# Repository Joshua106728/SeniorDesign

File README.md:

Aimed at helping composers and music learners transcribe music, Ear2Ink is a portable embedded system designed to convert acoustic guitar performances into MIDI files in real time. The device captures audio through a digital microphone, processes the signals on a microcontroller, and stores the resulting data on an SD card for sheet music generation. A keypad interface allows the user to start and stop recordings, and an LCD screen provides system feedback. By combining real-time audio processing with intuitive user interfacing, Ear2Ink offers musicians the freedom to transcribe and compose on the fly.

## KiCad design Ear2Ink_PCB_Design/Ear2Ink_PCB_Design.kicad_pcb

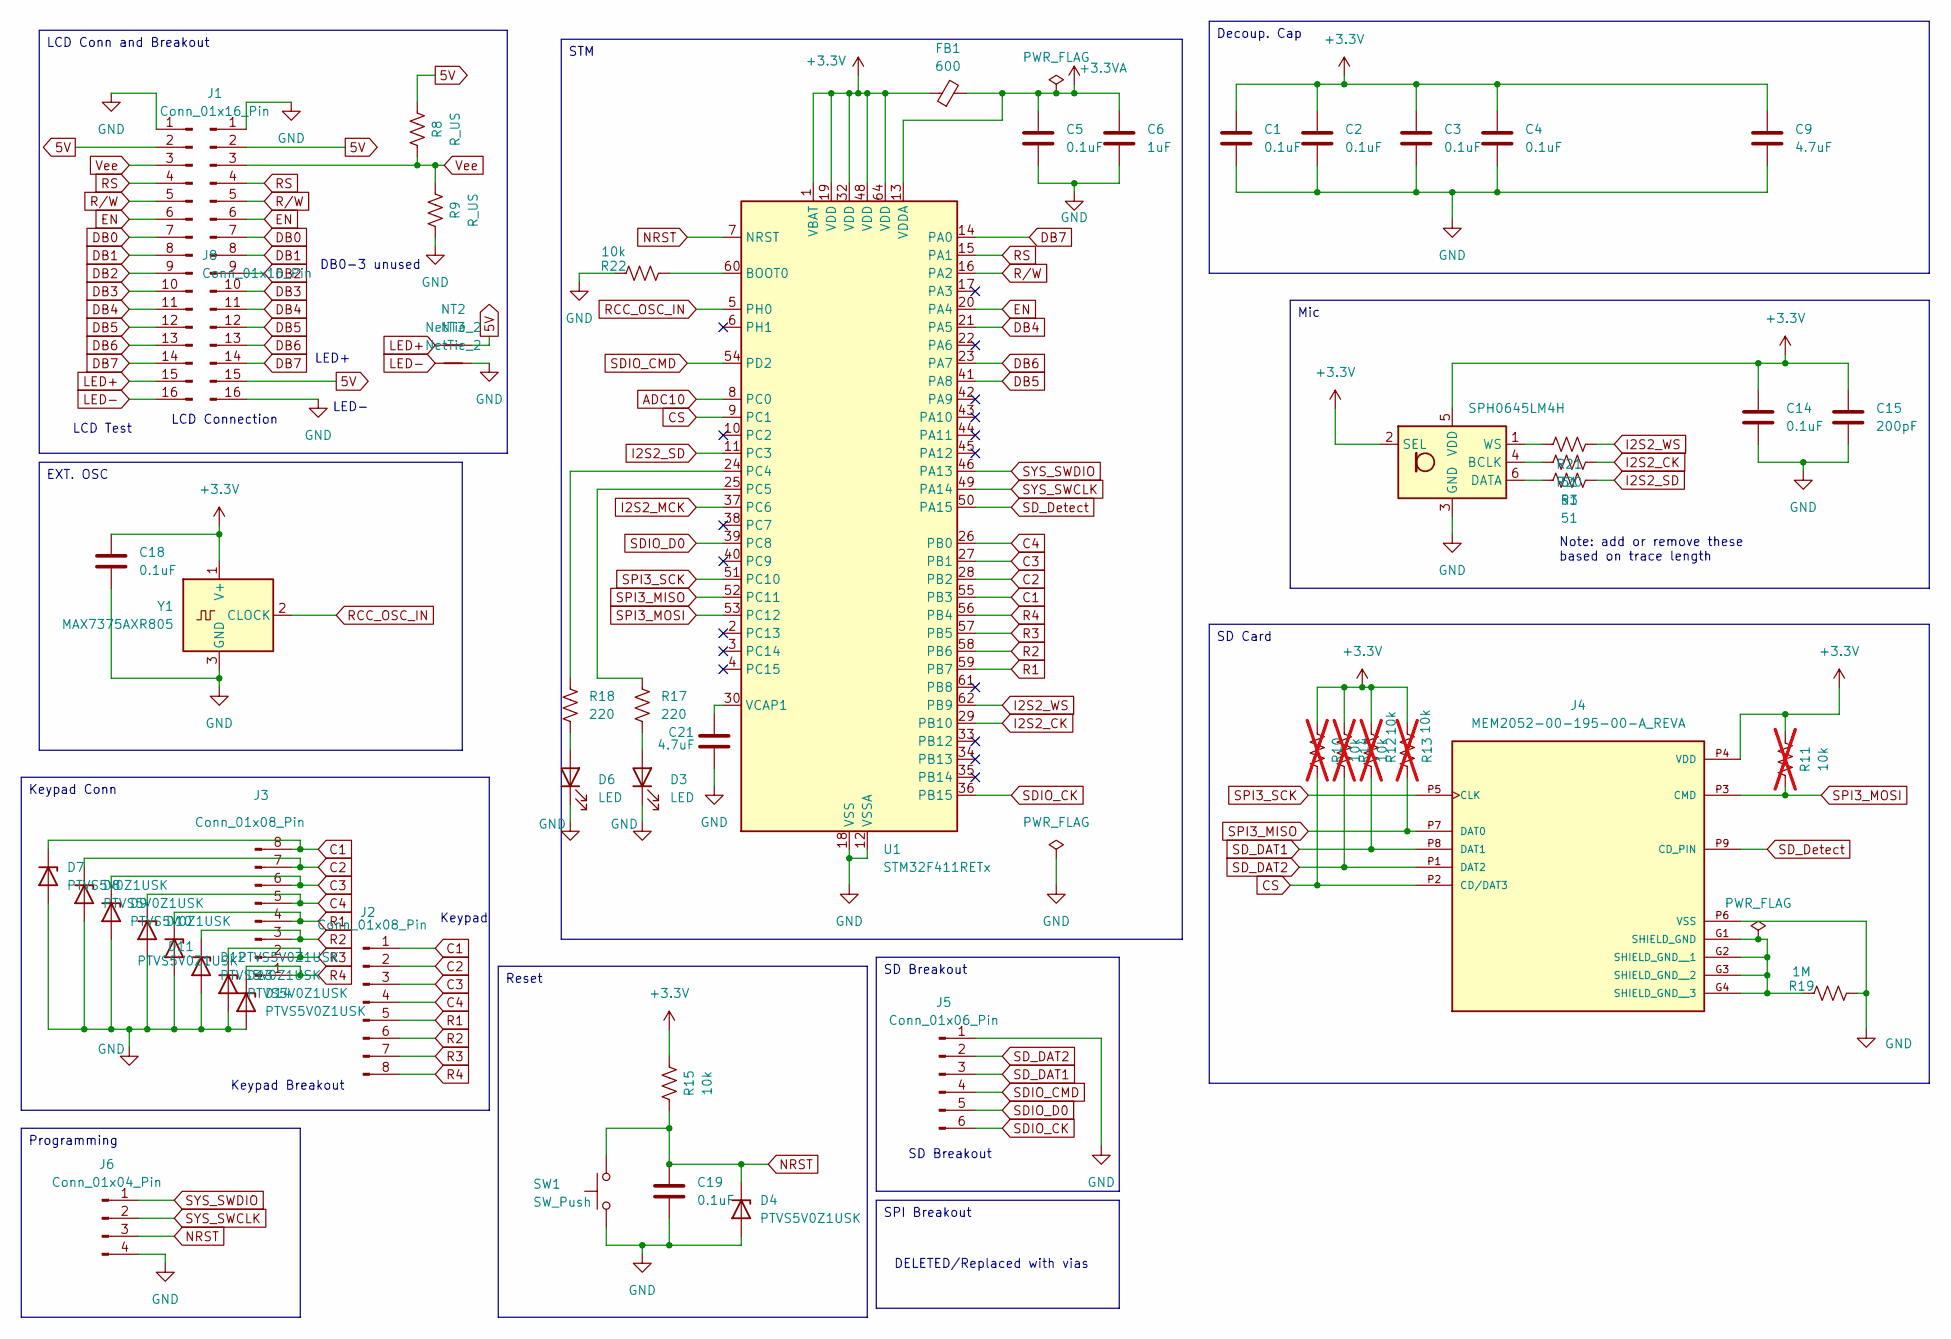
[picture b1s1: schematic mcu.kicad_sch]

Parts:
C1, C2, C3, C4, C5, C14, C18, C19: 0.1uF; C_0603_1608Metric_Pad1.08x0.95mm_HandSolder
C6: 1uF; C_0603_1608Metric_Pad1.08x0.95mm_HandSolder
C9, C21: 4.7uF; C_0603_1608Metric_Pad1.08x0.95mm_HandSolder
C15: 200pF; C_0805_2012Metric_Pad1.18x1.45mm_HandSolder
D3, D6: LED; LED_0805_2012Metric_Pad1.15x1.40mm_HandSolder
D4, D7, D8, D9, D10, D11, D12, D13, D14: PTVS5V0Z1USK; Nexperia_DSN1608-2_1.6x0.8mm
FB1: 600; R_0603_1608Metric_Pad0.98x0.95mm_HandSolder
J1, J8: Conn_01x16_Pin; PinHeader_1x16_P2.54mm_Vertical
J2, J3: Conn_01x08_Pin; PinHeader_1x08_P2.54mm_Vertical
J4: MEM2052-00-195-00-A_REVA; GCT_MEM2052-00-195-00-A_REVA; PARTREV A
J5: Conn_01x06_Pin; PinHeader_1x06_P2.54mm_Vertical
J6: Conn_01x04_Pin; PinHeader_1x04_P2.54mm_Vertical
MK1: SPH0645LM4H; Knowles_SPH0645LM4H-6_3.5x2.65mm
NT2, NT3: NetTie_2; NetTie-2_SMD_Pad0.5mm
R3, R20, R21: 51; R_0603_1608Metric_Pad0.98x0.95mm_HandSolder
R8, R9: R_US; R_0603_1608Metric_Pad0.98x0.95mm_HandSolder
R10, R11, R12, R13, R14: 10k; R_0603_1608Metric_Pad0.98x0.95mm_HandSolder; not fitted
R15, R22: 10k; R_0603_1608Metric_Pad0.98x0.95mm_HandSolder
R17, R18: 220; R_0603_1608Metric_Pad0.98x0.95mm_HandSolder
R19: 1M; R_0603_1608Metric_Pad0.98x0.95mm_HandSolder
SW1: SW_Push; SW_FSM2JMTR_TEC
U1: STM32F411RETx; LQFP64-10x10mm
Y1: MAX7375AXR805; SOT-323_SC-70

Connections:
5V: J1.2, J1.15, J8.2, NT2.2, R8.1; also elsewhere on the board
+3.3V: C1.1, C2.1, C3.1, C4.1, C9.1, C14.1, C15.1, C18.1, FB1.1, J4.P4 (VDD), MK1.2 (SEL), MK1.5 (VDD), R10.1, R11.1, R12.1, R13.1, R14.1, R15.1, U1.1 (VBAT), U1.19 (VDD), U1.32 (VDD), U1.48 (VDD), U1.64 (VDD), Y1.1 (V+); also elsewhere on the board
+3.3VA: C5.1, C6.1, FB1.2, U1.13 (VDDA)
ADC10: U1.8 (PC0); also elsewhere on the board
C1: D7.1 (K), J2.1, J3.8, U1.55 (PB3)
C2: D8.1 (K), J2.2, J3.7, U1.28 (PB2)
C3: D9.1 (K), J2.3, J3.6, U1.27 (PB1)
C4: D10.1 (K), J2.4, J3.5, U1.26 (PB0)
CS: J4.P2 (CD/DAT3), R10.2, U1.9 (PC1)
DB0: J1.7, J8.7
DB1: J1.8, J8.8
DB2: J1.9, J8.9
DB3: J1.10, J8.10
DB4: J1.11, J8.11, U1.21 (PA5)
DB5: J1.12, J8.12, U1.41 (PA8)
DB6: J1.13, J8.13, U1.23 (PA7)
DB7: J1.14, J8.14, U1.14 (PA0)
EN: J1.6, J8.6, U1.20 (PA4)
GND: C1.2, C2.2, C3.2, C4.2, C5.2, C6.2, C9.2, C14.2, C15.2, C18.2, C19.2, C21.2, D3.1 (K), D4.2 (A), D6.1 (K), D7.2 (A), D8.2 (A), D9.2 (A), D10.2 (A), D11.2 (A), D12.2 (A), D13.2 (A), D14.2 (A), J1.1, J1.16, J4.P6 (VSS), J5.1, J6.4, J8.1, MK1.3 (GND), NT3.2, R9.2, R19.2, R22.1, SW1.1, U1.12 (VSSA), U1.18 (VSS), U1.31 (VSS), U1.47 (VSS), U1.63 (VSS), Y1.3 (GND); also elsewhere on the board
I2S2_CK: R20.1, U1.29 (PB10)
I2S2_MCK: U1.37 (PC6)
I2S2_SD: R3.1, U1.11 (PC3)
I2S2_WS: R21.1, U1.62 (PB9)
LED+: J8.15, NT2.1
LED-: J8.16, NT3.1
NRST: C19.1, D4.1 (K), J6.3, R15.2, SW1.2, U1.7 (NRST)
unnamed: D3.2 (A), R17.2
unnamed: D6.2 (A), R18.2
unnamed: J4.G1 (SHIELD_GND), J4.G2 (SHIELD_GND__1), J4.G3 (SHIELD_GND__2), J4.G4 (SHIELD_GND__3), R19.1
unnamed: MK1.4 (BCLK), R20.2
unnamed: MK1.6 (DATA), R3.2
unnamed: MK1.1 (WS), R21.2
unnamed: R22.2, U1.60 (BOOT0)
unnamed: R18.1, U1.24 (PC4)
unnamed: R17.1, U1.25 (PC5)
unnamed: C21.1, U1.30 (VCAP1)
R1: D11.1 (K), J2.5, J3.4, U1.59 (PB7)
R2: D12.1 (K), J2.6, J3.3, U1.58 (PB6)
R3: D13.1 (K), J2.7, J3.2, U1.57 (PB5)
R4: D14.1 (K), J2.8, J3.1, U1.56 (PB4)
RCC_OSC_IN: U1.5 (PH0), Y1.2 (CLOCK)
RS: J1.4, J8.4, U1.15 (PA1)
R/W: J1.5, J8.5, U1.16 (PA2)
SDIO_CK: J5.6, U1.36 (PB15)
SDIO_CMD: J5.4, U1.54 (PD2)
SDIO_D0: J5.5, U1.39 (PC8)
SD_DAT1: J4.P8 (DAT1), J5.3, R12.2
SD_DAT2: J4.P1 (DAT2), J5.2, R14.2
SD_Detect: J4.P9 (CD_PIN), U1.50 (PA15)
SPI3_MISO: J4.P7 (DAT0), R13.2, U1.52 (PC11)
SPI3_MOSI: J4.P3 (CMD), R11.2, U1.53 (PC12)
SPI3_SCK: J4.P5 (CLK), U1.51 (PC10)
SYS_SWCLK: J6.2, U1.49 (PA14)
SYS_SWDIO: J6.1, U1.46 (PA13)
Vee: J1.3, J8.3, R8.2, R9.1

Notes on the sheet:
LED+
LCD Connection
Note: add or remove these based on trace length
LCD Test
LED-
SD Breakout
DELETED/Replaced with vias
DB0-3 unused
Keypad Breakout
Keypad
Mic
Keypad Conn
STM
Reset
Programming
SD Card
LCD Conn and Breakout
SPI Breakout
EXT. OSC
Decoup. Cap

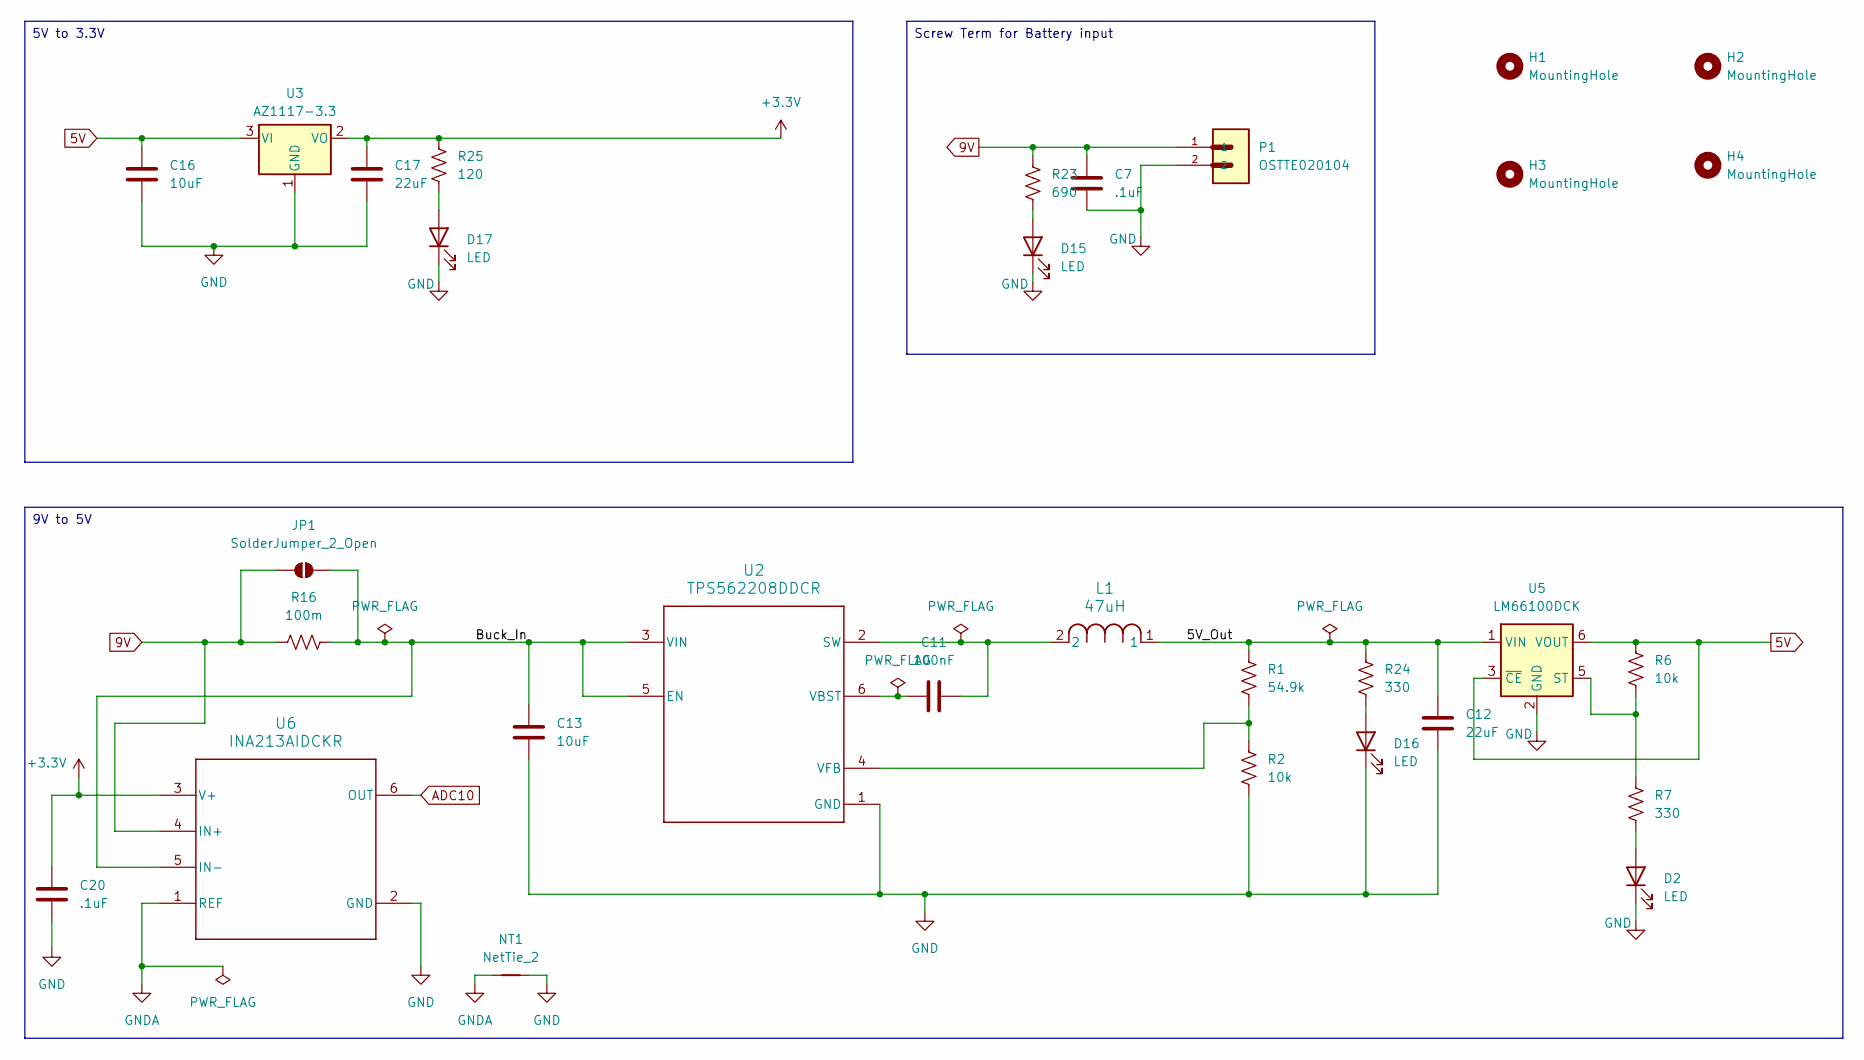
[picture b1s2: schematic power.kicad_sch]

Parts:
C7, C20: .1uF; C_0603_1608Metric_Pad1.08x0.95mm_HandSolder
C11: 100nF; C_0603_1608Metric_Pad1.08x0.95mm_HandSolder
C12, C17: 22uF; C_0603_1608Metric_Pad1.08x0.95mm_HandSolder
C13, C16: 10uF; C_0603_1608Metric_Pad1.08x0.95mm_HandSolder
D2, D15, D16, D17: LED; LED_0805_2012Metric_Pad1.15x1.40mm_HandSolder
H1, H2, H3, H4: MountingHole; MountingHole_2.5mm
JP1: SolderJumper_2_Open; SolderJumper-2_P1.3mm_Open_Pad1.0x1.5mm
L1: 47uH; L_Vishay_IFSC-1515AH_4x4x1.8mm
NT1: NetTie_2; NetTie-2_SMD_Pad0.5mm
P1: OSTTE020104; OST_OSTTE020104
R1: 54.9k; R_0603_1608Metric_Pad0.98x0.95mm_HandSolder
R2, R6: 10k; R_0603_1608Metric_Pad0.98x0.95mm_HandSolder
R7, R24: 330; R_0603_1608Metric_Pad0.98x0.95mm_HandSolder
R16: 100m; R_0603_1608Metric_Pad0.98x0.95mm_HandSolder
R23: 690; R_0603_1608Metric_Pad0.98x0.95mm_HandSolder
R25: 120; R_0603_1608Metric_Pad0.98x0.95mm_HandSolder
U2: TPS562208DDCR; DDC0006A_N
U3: AZ1117-3.3; SOT-223_DIO
U5: LM66100DCK; SOT-363_SC-70-6
U6: INA213AIDCKR; DCK0006A_N

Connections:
5V: C16.1, R6.1, U3.3 (VI), U5.3 (~CE), U5.6 (VOUT); also elsewhere on the board
9V: C7.2, JP1.1 (A), P1.1, R16.2, R23.1, U6.4 (IN+)
+3.3V: C17.1, C20.2, R25.1, U3.2 (VO), U6.3 (V+); also elsewhere on the board
/Power Conversions + Battery Monitor/5V_Out: C12.1, L1.1, R1.1, R24.1, U5.1 (VIN)
/Power Conversions + Battery Monitor/Buck_In: C13.2, JP1.2 (B), R16.1, U2.3 (VIN), U2.5 (EN), U6.5 (IN-)
ADC10: U6.6 (OUT); also elsewhere on the board
GND: C7.1, C12.2, C13.1, C16.2, C17.2, C20.1, D2.1 (K), D15.1 (K), D16.1 (K), D17.1 (K), NT1.2, P1.2, R2.2, U2.1 (GND), U3.1 (GND), U5.2 (GND), U6.2 (GND); also elsewhere on the board
GNDA: NT1.1, U6.1 (REF)
unnamed: D2.2 (A), R7.2
unnamed: D15.2 (A), R23.2
unnamed: D16.2 (A), R24.2
unnamed: D17.2 (A), R25.2
unnamed: C11.2, L1.2, U2.2 (SW)
unnamed: C11.1, U2.6 (VBST)
unnamed: R1.2, R2.1, U2.4 (VFB)
unnamed: R6.2, R7.1, U5.5 (ST)

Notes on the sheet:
Screw Term for Battery input
9V to 5V
5V to 3.3V

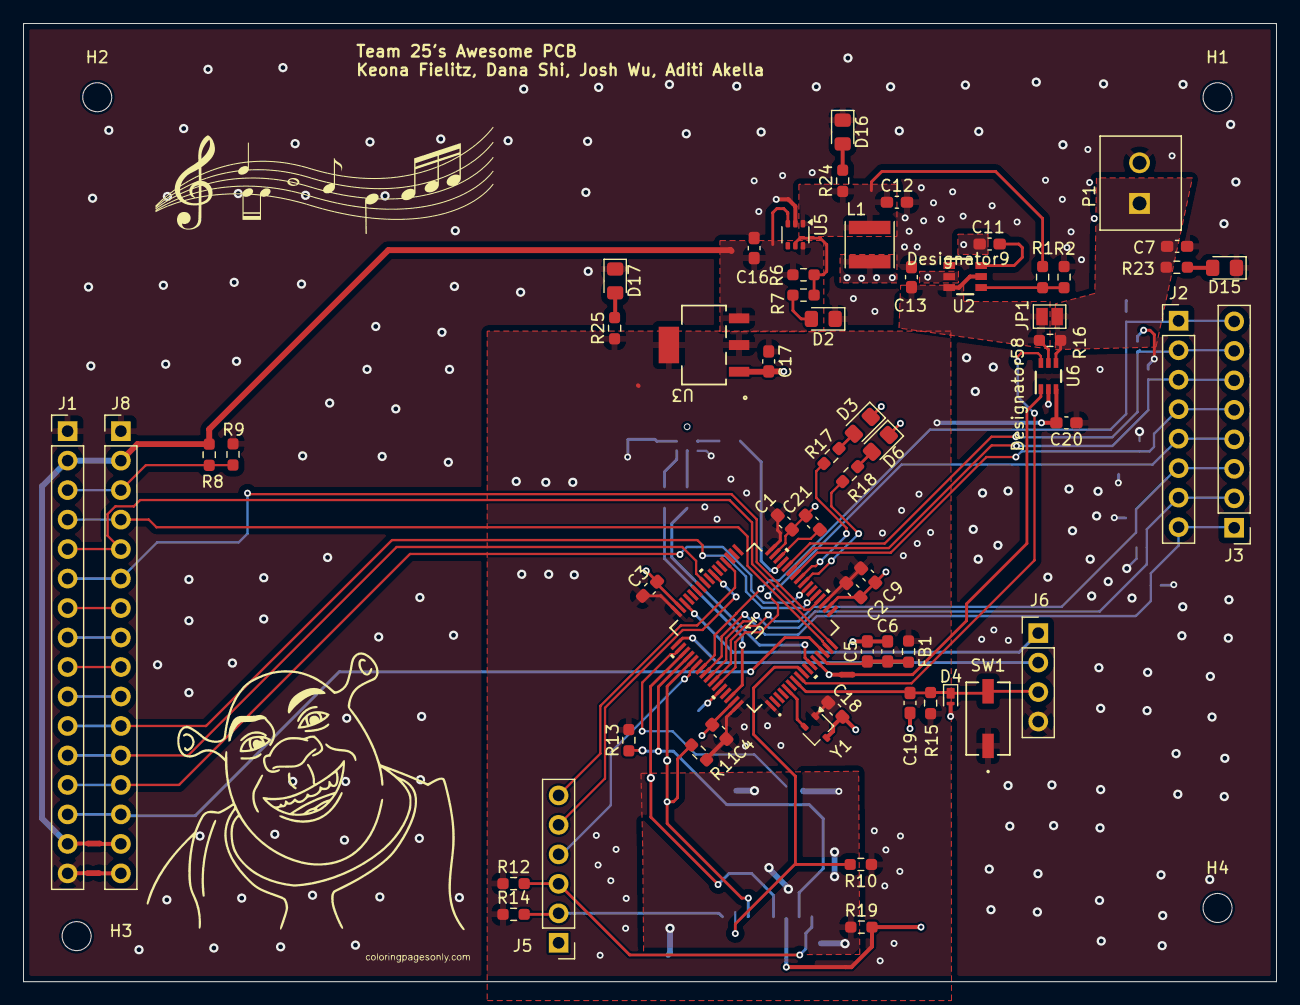
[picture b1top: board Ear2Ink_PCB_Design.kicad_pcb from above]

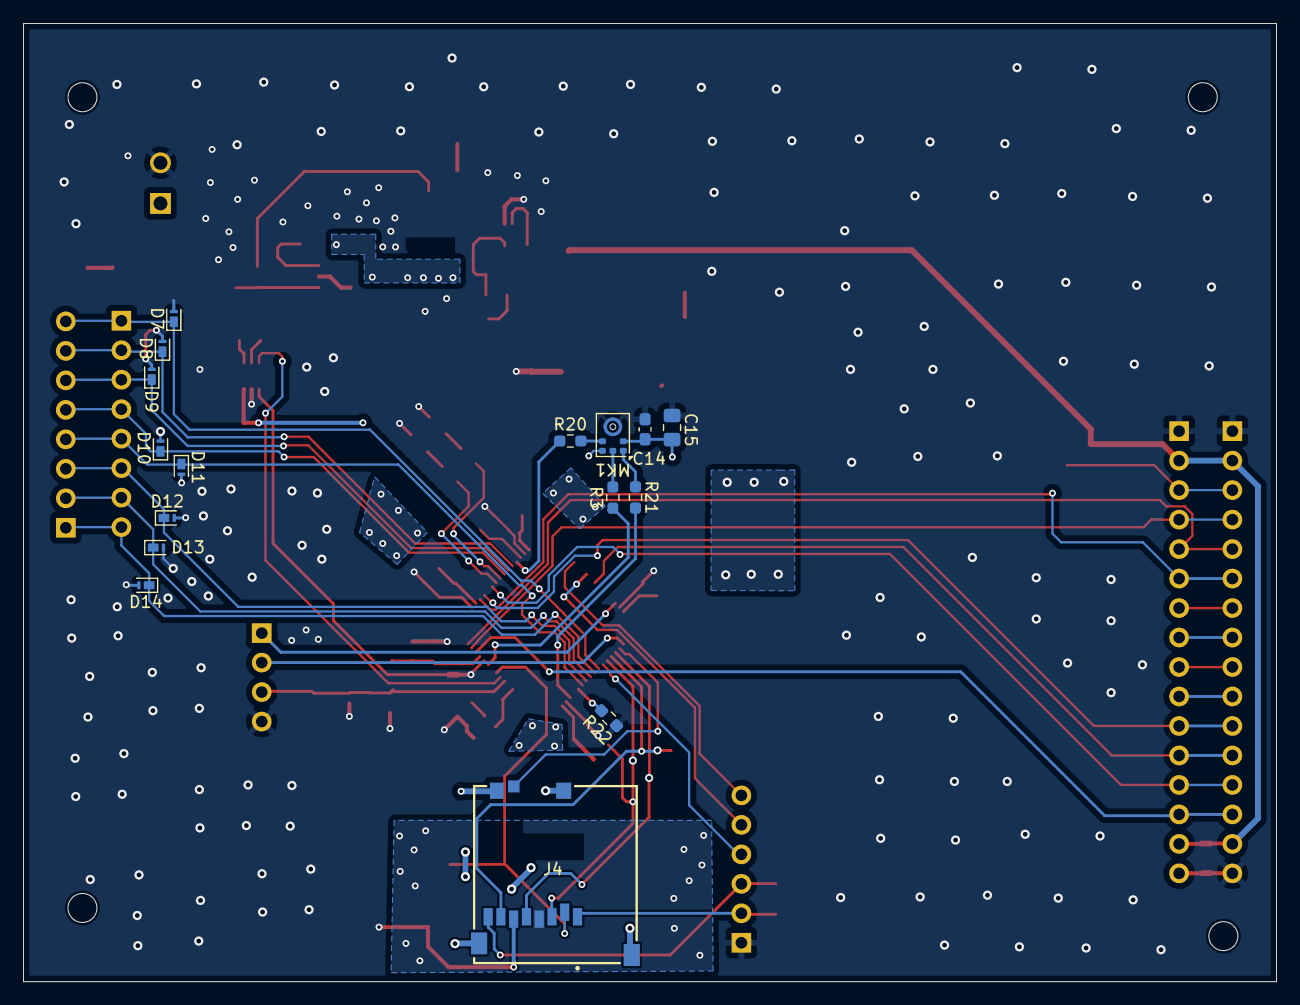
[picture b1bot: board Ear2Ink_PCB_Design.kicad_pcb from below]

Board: 2 copper layers, 108.0 x 82.5 mm, 83 parts (16 on the bottom side), 66 nets.

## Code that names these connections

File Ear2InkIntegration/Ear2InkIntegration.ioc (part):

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Mcu.Name=STM32F411R(C-E)Tx
Mcu.Package=LQFP64
Mcu.UserName=STM32F411RETx
PA0-WKUP.GPIOParameters=GPIO_Label
PA0-WKUP.GPIO_Label=DB7
PA0-WKUP.Signal=GPIO_Output
PA1.GPIOParameters=GPIO_Label
PA1.GPIO_Label=RS
PA1.Signal=GPIO_Output
PA13.Mode=Serial_Wire
PA13.Signal=SYS_JTMS-SWDIO
PA14.Mode=Serial_Wire
PA14.Signal=SYS_JTCK-SWCLK
PA15.GPIOParameters=GPIO_PuPd,GPIO_Label
PA15.GPIO_Label=SD_DETECT
PA15.GPIO_PuPd=GPIO_PULLUP
PA15.Signal=GPIO_Input
PA2.GPIOParameters=GPIO_Label
PA2.GPIO_Label=R/W
PA2.Signal=GPIO_Output
PA4.GPIOParameters=GPIO_Label
PA4.GPIO_Label=EN
PA4.Signal=GPIO_Output
PA5.GPIOParameters=GPIO_Label
PA5.GPIO_Label=DB4
PA5.Signal=GPIO_Output
PA7.GPIOParameters=GPIO_Label
PA7.GPIO_Label=DB6
PA7.Signal=GPIO_Output
PA8.GPIOParameters=GPIO_Label
PA8.GPIO_Label=DB5
PA8.Signal=GPIO_Output
PB0.GPIOParameters=GPIO_PuPd,GPIO_Label
PB0.GPIO_Label=C4
PB0.GPIO_PuPd=GPIO_PULLUP
PB0.Signal=GPIO_Input
PB1.GPIOParameters=GPIO_PuPd,GPIO_Label,GPIO_ModeDefaultEXTI
PB1.GPIO_Label=C3
PB1.GPIO_ModeDefaultEXTI=GPIO_MODE_IT_FALLING
PB1.GPIO_PuPd=GPIO_PULLUP
PB1.Signal=GPXTI1
PB10.Mode=Half_Duplex_Master
PB10.Signal=I2S2_CK
PB2.GPIOParameters=GPIO_PuPd,GPIO_Label
PB2.GPIO_Label=C2
PB2.GPIO_PuPd=GPIO_PULLUP
PB2.Signal=GPIO_Input
PB3.GPIOParameters=GPIO_PuPd,GPIO_Label,GPIO_ModeDefaultEXTI
PB3.GPIO_Label=C1
PB3.GPIO_ModeDefaultEXTI=GPIO_MODE_IT_FALLING
PB3.GPIO_PuPd=GPIO_PULLUP
PB3.Signal=GPXTI3
PB4.GPIOParameters=PinState,GPIO_Label
PB4.GPIO_Label=R4
PB4.PinState=GPIO_PIN_SET
PB4.Signal=GPIO_Output
PB5.GPIOParameters=PinState,GPIO_Label
PB5.GPIO_Label=R3
PB5.PinState=GPIO_PIN_SET
PB5.Signal=GPIO_Output
PB6.GPIOParameters=PinState,GPIO_Label
PB6.GPIO_Label=R2
PB6.PinState=GPIO_PIN_SET
PB6.Signal=GPIO_Output
PB7.GPIOParameters=PinState,GPIO_Label
PB7.GPIO_Label=R1
PB7.PinState=GPIO_PIN_SET
PB7.Signal=GPIO_Output
PB9.Mode=Half_Duplex_Master
PB9.Signal=I2S2_WS
PC1.GPIOParameters=PinState,GPIO_Label
PC1.GPIO_Label=CS
PC1.PinState=GPIO_PIN_SET
PC1.Signal=GPIO_Output
PC10.Mode=Full_Duplex_Master
PC10.Signal=SPI3_SCK
PC11.Mode=Full_Duplex_Master
PC11.Signal=SPI3_MISO
PC12.Mode=Full_Duplex_Master
PC12.Signal=SPI3_MOSI
PC3.Mode=Half_Duplex_Master
PC3.Signal=I2S2_SD
PC4.GPIOParameters=GPIO_Label
PC4.GPIO_Label=LED1
PC4.Signal=GPIO_Output
PC5.GPIOParameters=GPIO_Label
PC5.GPIO_Label=MET
PC5.Signal=GPIO_Output
RCC.HSE_VALUE=25000000
RCC.SYSCLKFreq_VALUE=96000000
RCC.SYSCLKSource=RCC_SYSCLKSOURCE_PLLCLK
board=custom

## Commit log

2025-10-01 initial push
    code contains a sine wave generator and currently just the YIN algorithm to detect fundamental frequency
2025-10-04 initial code
2025-10-07 time encoding in MIDI not correct HALP
2025-10-09 audo to midi not work still
2025-10-13 twinkle twinkle little stars working
2025-10-17 moving files
2026-01-22 Removed Python, added KiCad
2026-01-22 added buck
2026-01-23 added some stuff
2026-01-24 added osc
2026-01-26 added voltage prot
2026-01-31 wired LCD and keypad
2026-02-04 everything except voltage monitor on schematic
    no footprints assigned yet
2026-02-05 started assigning footprints
2026-02-05 added esd prot and programming header
2026-02-06 footprints
    missing L tho
2026-02-07 all footprints done
2026-02-07 added current monitor
2026-02-09 working on erc errors
2026-02-09 fixed erc stuff
2026-02-10 SDIO to SPI
2026-02-10 added zip file for archived proj
2026-02-11 fixed footprint issue with SD
2026-02-11 footprints loaded into pcb
2026-02-12 components on board (no traces yet)
2026-02-12 some routing
2026-02-14 some pcb
2026-02-15 more progress
2026-02-15 ran DRC and fixed some errors
2026-02-16 fixed everything
2026-02-16 added archived file
2026-02-17 changed some resistor values NEED To UPDATE LAYOUT
2026-02-17 resistors changed UPDATE LAYOUT
2026-02-27 New Parts Added
2026-02-27 Did a lot of stuff
2026-03-01 put everything on not done tho
    almost done
2026-03-02 working through DRC, routing done
2026-03-03 finshed routing and minimal drc
2026-03-03 made project archive for review
2026-03-06 done
2026-03-06 updated 5V resistor values
2026-03-06 archive
2026-03-07 untented vias added
2026-03-13 flipped SD to the other side
2026-03-13 added pic
2026-03-13 fab outputs
2026-03-25 working on python --> c wrapper
2026-03-31 all python should be working
2026-04-22 keylad lcd mic working - sd dsp need some work
2026-04-22 added midi file writing after stop is pressed
2026-04-30 final changes
2026-04-30 Add project overview to README.md
    Added project description for Ear2Ink system.
